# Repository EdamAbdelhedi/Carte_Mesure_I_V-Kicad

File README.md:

La carte de mesures électriques a été réalisée pendant mon stage d’ingénieur, du 18 juin au 27 juillet 2024, au sein du Laboratoire des Systèmes Électriques de l’ENIT, sous l’encadrement de monsieur Mohamed Wissem Naouar.

Cette carte se compose de deux blocs :

Bloc de mesure de courant

Bloc de mesure de tension

****Pour le premier bloc, nous avons utilisé le capteur LA55-P, permettant la mesure de courants jusqu'à 50 A.
Ce bloc est composé de trois étages :

Capteur de courant LA55-P avec sa résistance de mesure

Amplificateur passe-bas inverseur

Soustracteur différentiel (permet d’ajouter un décalage supplémentaire de 1,5 V au signal d’entrée)

Bloc de mesure de tension

****Pour le deuxième bloc, nous avons utilisé le capteur LV25-P, permettant la mesure de tensions jusqu'à ±500 V.
Ce bloc est composé de trois étages :

Capteur de tension LV25-P avec sa résistance de mesure

Suiveur pour assurer une adaptation d’impédance

Filtre passe-bas inverseur (permet de supprimer les bruits électriques et les interférences pouvant affecter la mesure de tension)

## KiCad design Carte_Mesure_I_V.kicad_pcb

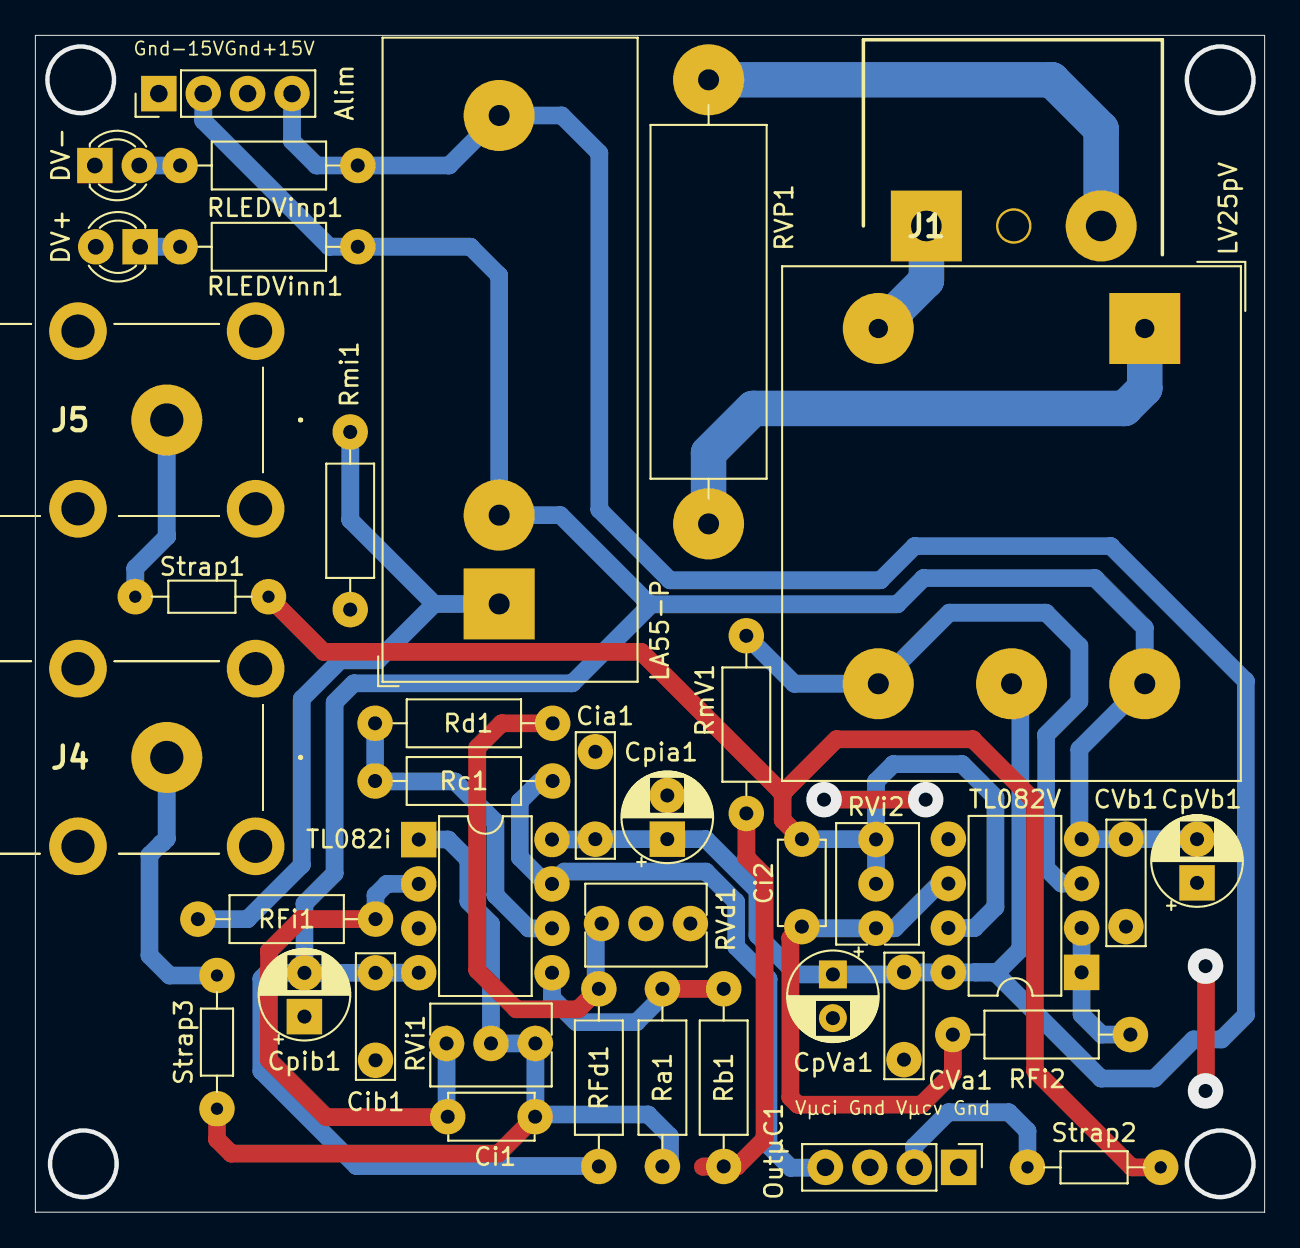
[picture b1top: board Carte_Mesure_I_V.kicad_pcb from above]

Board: 2 copper layers, 70.3 x 67.3 mm, 39 parts (0 on the bottom side), 22 nets.

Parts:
Alim: Alim; PinHeader_1x04_P2.54mm_Vertical
CVa1: 100n; C_Rect_L7.0mm_W2.0mm_P5.00mm
CVb1: 100n; C_Rect_L7.0mm_W2.0mm_P5.00mm
Ci1: 220p; C_Disc_D4.7mm_W2.5mm_P5.00mm
Ci2: 4.7n; C_Disc_D4.7mm_W2.5mm_P5.00mm
Cia1: 100n; C_Rect_L7.0mm_W2.0mm_P5.00mm
Cib1: 100n; C_Rect_L7.0mm_W2.0mm_P5.00mm
CpVa1: 1µ; CP_Radial_D5.0mm_P2.50mm
CpVb1: 1µ; CP_Radial_D5.0mm_P2.50mm
Cpia1: 1µ; CP_Radial_D5.0mm_P2.50mm
Cpib1: 1µ; CP_Radial_D5.0mm_P2.50mm
DV+: LED; LED_D3.0mm
DV-: LED; LED_D3.0mm
J1: BorV; 2350513-3
J4: BNCi_osc; BNCLRPC140
J5: BNCV_osc; BNCLRPC140
LA55-P: LA55-P; LEM_LA25-P
LV25pV: LV25pV; LEM_LV25-P
OutµC1: OutµC; PinHeader_1x04_P2.54mm_Vertical
RFd1: 1k; R_Axial_DIN0207_L6.3mm_D2.5mm_P10.16mm_Horizontal
RFi1: 10k; R_Axial_DIN0207_L6.3mm_D2.5mm_P10.16mm_Horizontal
RFi2: 4.7k; R_Axial_DIN0207_L6.3mm_D2.5mm_P10.16mm_Horizontal
RLEDVinn1: 10k; R_Axial_DIN0207_L6.3mm_D2.5mm_P10.16mm_Horizontal
RLEDVinp1: 10k; R_Axial_DIN0207_L6.3mm_D2.5mm_P10.16mm_Horizontal
RVP1: 47k-5W; R_Axial_Power_L20.0mm_W6.4mm_P25.40mm
RVd1: 0.2k; Potentiometer_Bourns_3266Y_Vertical
RVi1, RVi2: 10k; Potentiometer_Bourns_3266Y_Vertical
Ra1: 20k; R_Axial_DIN0207_L6.3mm_D2.5mm_P10.16mm_Horizontal
Rb1: 20k; R_Axial_DIN0207_L6.3mm_D2.5mm_P10.16mm_Horizontal
Rc1: 20k; R_Axial_DIN0207_L6.3mm_D2.5mm_P10.16mm_Horizontal
Rd1: 20k; R_Axial_DIN0207_L6.3mm_D2.5mm_P10.16mm_Horizontal
RmV1: 120; R_Axial_DIN0207_L6.3mm_D2.5mm_P10.16mm_Horizontal
Rmi1: 60; R_Axial_DIN0207_L6.3mm_D2.5mm_P10.16mm_Horizontal
Strap1, Strap2, Strap3: R_Axial_DIN0204_L3.6mm_D1.6mm_P7.62mm_Horizontal
TL082V: TL082V; DIP-8_W7.62mm
TL082i: TL082i; DIP-8_W7.62mm

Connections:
+15V: Alim.4, CVa1.1, Cia1.1, CpVa1.1, Cpia1.1, LA55-P.3 (+), LV25pV.5 (V+), RLEDVinp1.1, TL082V.8 (V+), TL082i.8 (V+)
-15V: Alim.2, CVb1.1, Cib1.1, CpVb1.2, Cpib1.2, LA55-P.2 (-), LV25pV.6 (V-), RFd1.1, RLEDVinn1.1, TL082V.4 (V-), TL082i.4 (V-)
GND: Alim.1, Alim.3, CVa1.2, CVb1.2, Cia1.2, Cib1.2, CpVa1.2, CpVb1.1, Cpia1.2, Cpib1.1, DV+.2 (A), DV-.1 (K), J4.2, J4.3, J4.4, J4.5, J5.2, J5.3, J5.4, J5.5, OutµC1.1, OutµC1.3, RVd1.1, RVd1.2, Rb1.2, RmV1.2, Rmi1.2, TL082V.5 (+), TL082i.3 (+)
unnamed: DV+.1 (K), RLEDVinn1.2
unnamed: DV-.2 (A), RLEDVinp1.2
unnamed: J1.3, RVP1.1
unnamed: J4.1, Strap3.2
unnamed: J5.1, Strap1.2
unnamed: OutµC1.2, Strap2.1
unnamed: RFd1.2, RVd1.3, Rc1.1
unnamed: LA55-P.1 (M), RFi1.1, Rmi1.1
unnamed: LV25pV.1 (HV+), RVP1.2
unnamed: J1.1, LV25pV.3 (HV-)
unnamed: LV25pV.4 (M), RmV1.1, TL082V.3 (+)
unnamed: RFi2.1, TL082V.1, TL082V.2 (-)
unnamed: Ci2.1, RFi2.2, RVi2.3, TL082V.6 (-)
unnamed: Ci1.1, RFi1.2, RVi1.3, TL082i.2 (-)
unnamed: Ra1.2, Rb1.1, TL082i.5 (+)
unnamed: Rc1.2, Rd1.1, TL082i.6 (-)
Vosc_i: Ci1.2, RVi1.1, RVi1.2, Ra1.1, Strap3.1, TL082i.1
Vosc_µc_V: Ci2.2, RVi2.1, RVi2.2, Strap1.1, Strap2.2, TL082V.7
Vµc_i: OutµC1.4, Rd1.2, TL082i.7

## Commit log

2025-12-11 README.md
